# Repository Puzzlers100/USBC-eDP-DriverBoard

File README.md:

## __USBC-eDP Driver Board__  

This project works to adapt a USB-C DisplayPort alt-mode input into an embedded DisplayPort output. It uses an STM32 to communicate over the USB-C Power delivery protocol, acts as a USB Hub providing one USB 3.0 Superspeed port and 2 USB 2.0 High Speed ports. It also negotiates the highest current available from the source, and internally generates the 12V needed to run the display.  It works by simply routing the same DP signals through to the output, and does no signal processing of it's own. 
## USE  

It should work with most 30pin eDP panels. Since it has no native processing on it's own, the DP generation is set by the computer and panel used. Generally, this allows for up to 1080p panels. Exceptionally large or exceptionally bright panels may not work, as those panels tend to draw a large current on the 12V rail. I highly recommend sticking to panels that draw a continuous current of no more than 800mA for the backlight.

The STM32 provides PWM dimming capability by using the potentiometer on the daughter board. If you want to remove this capability, short pin 1 to pin 2 on J2 (This is a temporary solution, the plan is to in the future specify which brightness control scheme should be used using R25 and R26)

Personally, I am using the Innolux N116BCA-EA1 panel with a 3D printed case published in the Mechanical folder. If you would prefer a 1080p panel, the AUO G116HAN looks like it should also fit the case, however I do not have one to test with. 

#### NOTICE
The USB 2.0 ports are configured to run outside of the USB specification. They claim to be able to provide up to 500mA of current, however trigger overcurrent protection at 250mA. This can be fixed by replacing line 17 in i2C_comms.c with {0x18, 0x20, 0x01}, however the incorrect version can be useful with higher power flash drives that require 200mA, which was the reason I chose to do it this way.
## BUILD INFO

#### PCBs
BOMs for both the main board and secondary board are in the electrical folder, and contain all the parts required to build a fully functional PCB.  The main board is specifically designed to be manufactured using JLC-PCBs JLC04081H-3313 stackup, as the USB lines are impedance matched, and the generated gerber files are designed to be used with JLC. The potentiometer board has no such restrictions, but I recommend using a 0.8mm PCB. Currently there is no pick and place support, so you will need to hand solder the PCBs. The passives should be rated for at least 12V

## Firmware
The firmware is written using the STMCube Ide. To get the PCB to work, you need to compile it using cube IDE, then upload it to the STM32 using either a J-link or STlink. If you have a TagConnect TC2030, there is a pad connector available on the PCB, if not, the pads are big enough you could solder on some leads to them.

## FFC cables
The design uses a Type A, 4pin, 0.5mm pitch FFC cable to connect the main board and pot board. For my design, I used a 10cm long cable, though what length you need may depend on your chosen LCD and layout

You will also require a 30 pin eDP cable. I used a 250mm one for my design.

## Hardware
The mechanical design is published as a set of solidworks files as well as a set of 3MFs. The 3MFs were made for the Prusa MK3S+ with the MMU2, though they will likely work with most slicers and printers that support multi filament printing. They are designed to be printed in PETG with appropriate scaling to account for shrinkage. A couple of the parts also have support blocks with a PLA interface so they should be removable. 

To fully assemble the enclosure, you will need:

- 19x [M2 4.8mm Wide, 1.5mm thick nuts](https://www.mcmaster.com/92513A110/)
- 13x [M2 10mm Countersunk Screw](https://www.mcmaster.com/90236A106/)
- 17x [M2 6mm Countersunk Screw](https://www.mcmaster.com/90236A104/)
- 13x [M2 4mm Countersunk Screw](https://www.mcmaster.com/90236A102/) 
	
## TODO
Future Plans are mostly in the software:
 - USB HID interface for brightness control and notifications
 - Proper current monitoring and active over-current protection control by reducing screen brightness
 - Use R25 and R26 resistors to define which brightness control method is desired.
 - Redesign the enclosure to use metal nuts. I just used some nuts I had on hand that I thought were M2 but are actually probably M2.5

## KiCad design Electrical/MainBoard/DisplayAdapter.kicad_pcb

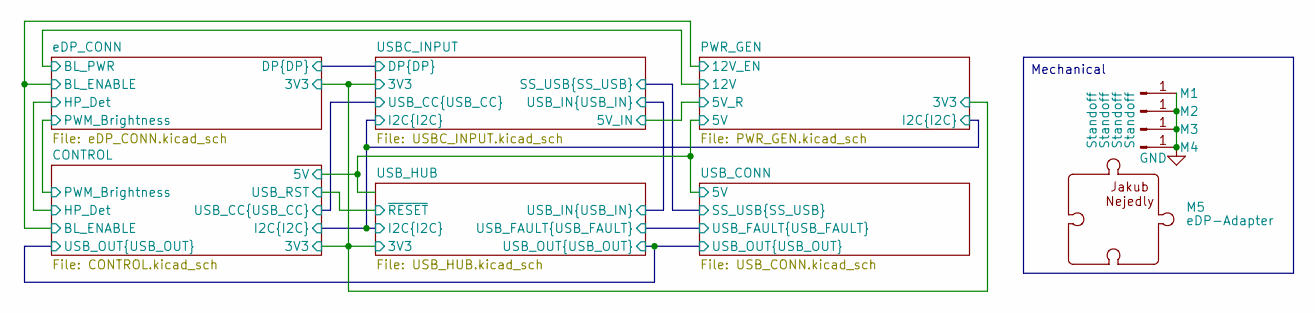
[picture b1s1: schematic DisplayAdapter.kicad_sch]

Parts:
M1, M2, M3, M4: Standoff; MS04-M2-2
M5: eDP-Adapter; Logo

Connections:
GND: M1.1, M2.1, M3.1, M4.1; also elsewhere on the board

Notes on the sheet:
Mechanical

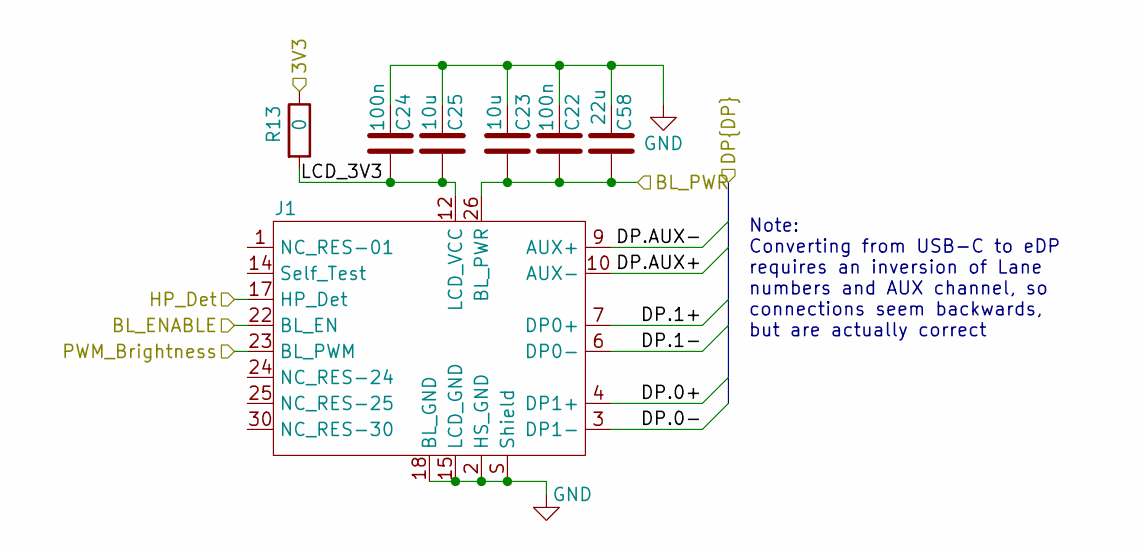
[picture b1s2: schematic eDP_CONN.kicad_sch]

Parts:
C22, C24: 100n; 0603_C
C23, C25: 10u; 0603_C
C58: 22u; 0603_C
J1: 30_Pin_Zif; FH19SC-30S-0.5SH(09)
R13: 0; 0805_R

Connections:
/CONTROL/3V3: R13.1; also elsewhere on the board
/CONTROL/BL_ENABLE: J1.22 (BL_EN); also elsewhere on the board
/CONTROL/HP_Det: J1.17 (HP_Det); also elsewhere on the board
/CONTROL/PWM_Brightness: J1.23 (BL_PWM); also elsewhere on the board
/PWR_GEN/12V: C22.2, C23.2, C58.2, J1.26 (BL_PWR), J1.27 (BL_PWR), J1.28 (BL_PWR), J1.29 (BL_PWR); also elsewhere on the board
/USBC_INPUT/DP.0+: J1.4 (DP1+); also elsewhere on the board
/USBC_INPUT/DP.0-: J1.3 (DP1-); also elsewhere on the board
/USBC_INPUT/DP.1+: J1.7 (DP0+); also elsewhere on the board
/USBC_INPUT/DP.1-: J1.6 (DP0-); also elsewhere on the board
/USBC_INPUT/DP.AUX+: J1.10 (AUX-); also elsewhere on the board
/USBC_INPUT/DP.AUX-: J1.9 (AUX+); also elsewhere on the board
/eDP_CONN/LCD_3V3: C24.1, C25.1, J1.12 (LCD_VCC), J1.13 (LCD_VCC), R13.2
GND: C22.1, C23.1, C24.2, C25.2, C58.1, J1.2 (HS_GND), J1.5 (HS_GND), J1.8 (HS_GND), J1.11 (HS_GND), J1.15 (LCD_GND), J1.16 (LCD_GND), J1.18 (BL_GND), J1.19 (BL_GND), J1.20 (BL_GND), J1.21 (BL_GND), J1.S (Shield); also elsewhere on the board

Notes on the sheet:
Note: Converting from USB-C to eDP requires an inversion of Lane numbers and AUX channel, so connections seem backwards, but are actually correct

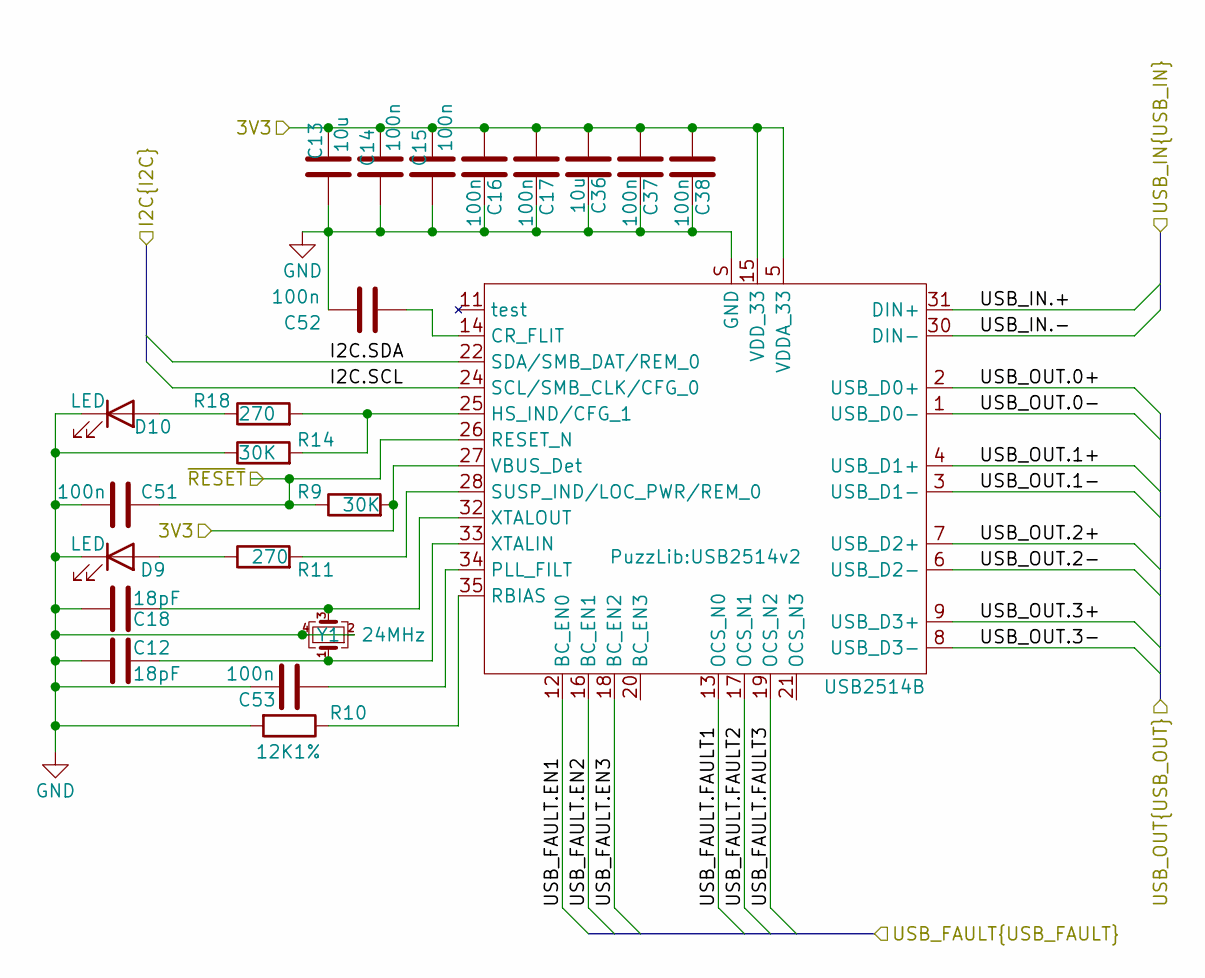
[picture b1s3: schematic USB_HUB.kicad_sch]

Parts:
C12, C18: 18pF; 0603_C
C13, C36: 10u; 0603_C
C14, C15, C16, C17, C37, C38, C51, C52, C53: 100n; 0603_C
D9, D10: LED; LTST_Diode
R9, R14: 30K; 0603_R
R10: 12K1%; 0603_R
R11, R18: 270; 0603_R
U5: USB2514B; USB2514v2
Y1: 24MHz; FA-128_OSC

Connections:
/CONTROL/3V3: C13.2, C14.2, C15.2, C16.2, C17.2, C36.2, C37.2, C38.2, R9.2, U5.5 (VDDA_33), U5.10 (VDDA_33), U5.15 (VDD_33), U5.23 (VDD_33), U5.27 (VBUS_Det), U5.29 (VDDA_33), U5.36 (VDDA_33); also elsewhere on the board
/CONTROL/I2C.SCL: U5.24 (SCL/SMB_CLK/CFG_0); also elsewhere on the board
/CONTROL/I2C.SDA: U5.22 (SDA/SMB_DAT/REM_0); also elsewhere on the board
/CONTROL/USB_OUT.0+: U5.2 (USB_D0+); also elsewhere on the board
/CONTROL/USB_OUT.0-: U5.1 (USB_D0-); also elsewhere on the board
/CONTROL/USB_OUT.1+: U5.4 (USB_D1+); also elsewhere on the board
/CONTROL/USB_OUT.1-: U5.3 (USB_D1-); also elsewhere on the board
/CONTROL/USB_OUT.2+: U5.7 (USB_D2+); also elsewhere on the board
/CONTROL/USB_OUT.2-: U5.6 (USB_D2-); also elsewhere on the board
/CONTROL/USB_OUT.3+: U5.9 (USB_D3+); also elsewhere on the board
/CONTROL/USB_OUT.3-: U5.8 (USB_D3-); also elsewhere on the board
/CONTROL/USB_RST: C51.1, R9.1, U5.26 (RESET_N); also elsewhere on the board
/USBC_INPUT/USB_IN.+: U5.31 (DIN+); also elsewhere on the board
/USBC_INPUT/USB_IN.-: U5.30 (DIN-); also elsewhere on the board
/USB_CONN/USB_FAULT.EN1: U5.12 (BC_EN0); also elsewhere on the board
/USB_CONN/USB_FAULT.EN2: U5.16 (BC_EN1); also elsewhere on the board
/USB_CONN/USB_FAULT.EN3: U5.18 (BC_EN2); also elsewhere on the board
/USB_CONN/USB_FAULT.FAULT1: U5.13 (OCS_N0); also elsewhere on the board
/USB_CONN/USB_FAULT.FAULT2: U5.17 (OCS_N1); also elsewhere on the board
/USB_CONN/USB_FAULT.FAULT3: U5.19 (OCS_N2); also elsewhere on the board
GND: C12.2, C13.1, C14.1, C15.1, C16.1, C17.1, C18.2, C36.1, C37.1, C38.1, C51.2, C52.2, C53.2, D9.1 (K), D10.1 (K), R10.2, R14.1, U5.S (GND), Y1.2, Y1.4; also elsewhere on the board
unnamed: D9.2 (A), R11.1
unnamed: D10.2 (A), R18.1
unnamed: C52.1, U5.14 (CR_FLIT)
unnamed: R14.2, R18.2, U5.25 (HS_IND/CFG_1)
unnamed: C53.1, U5.34 (PLL_FILT)
unnamed: R10.1, U5.35 (RBIAS)
unnamed: R11.2, U5.28 (SUSP_IND/LOC_PWR/REM_0)
unnamed: C12.1, U5.33 (XTALIN), Y1.1
unnamed: C18.1, U5.32 (XTALOUT), Y1.3

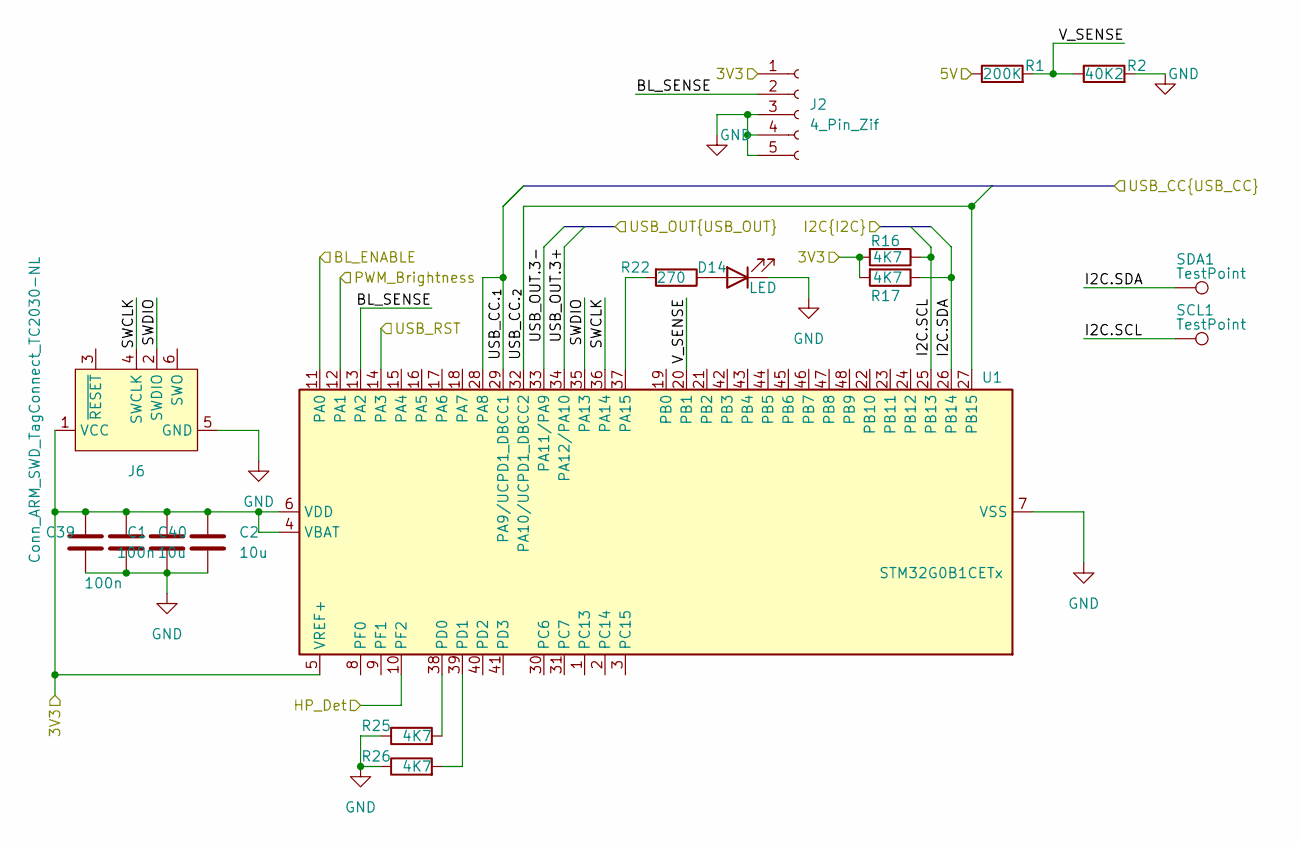
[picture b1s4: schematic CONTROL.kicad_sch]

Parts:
C1, C39: 100n; 0603_C
C2, C40: 10u; 0603_C
D14: LED; LTST_Diode
J2: 4_Pin_Zif; FH19C-4S-0.5SH(10)
J6: Conn_ARM_SWD_TagConnect_TC2030-NL; Tag-Connect_TC2030-IDC-NL_2x03_P1.27mm_Vertical
R1: 200K; 0603_R
R2: 40K2; 0603_R
R16, R17, R25, R26: 4K7; 0603_R
R22: 270; 0603_R
SCL1: TestPoint; TestPoint_Pad_D1.0mm
SDA1: TestPoint; TestPoint_Pad_D1.0mm
U1: STM32G0B1CETx; LQFP-48_7x7mm_P0.5mm

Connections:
/CONTROL/3V3: C1.1, C2.1, C39.1, C40.1, J2.1, J6.1 (VCC), R16.2, R17.2, U1.4 (VBAT), U1.5 (VREF+), U1.6 (VDD); also elsewhere on the board
/CONTROL/BL_ENABLE: U1.11 (PA0); also elsewhere on the board
/CONTROL/BL_SENSE: J2.2, U1.13 (PA2)
/CONTROL/HP_Det: U1.10 (PF2); also elsewhere on the board
/CONTROL/I2C.SCL: R16.1, SCL1.1, U1.25 (PB13); also elsewhere on the board
/CONTROL/I2C.SDA: R17.1, SDA1.1, U1.26 (PB14); also elsewhere on the board
/CONTROL/PWM_Brightness: U1.12 (PA1); also elsewhere on the board
/CONTROL/SWCLK: J6.4 (SWCLK), U1.36 (PA14)
/CONTROL/SWDIO: J6.2 (SWDIO), U1.35 (PA13)
/CONTROL/USB_CC._{1}: U1.28 (PA8), U1.29 (PA9/UCPD1_DBCC1); also elsewhere on the board
/CONTROL/USB_CC._{2}: U1.27 (PB15), U1.32 (PA10/UCPD1_DBCC2); also elsewhere on the board
/CONTROL/USB_OUT.3+: U1.34 (PA12/PA10); also elsewhere on the board
/CONTROL/USB_OUT.3-: U1.33 (PA11/PA9); also elsewhere on the board
/CONTROL/USB_RST: U1.14 (PA3); also elsewhere on the board
/CONTROL/V_SENSE: R1.2, R2.1, U1.20 (PB1)
/PWR_GEN/5V: R1.1; also elsewhere on the board
GND: C1.2, C2.2, C39.2, C40.2, D14.1 (K), J2.3, J2.4, J2.5, J6.5 (GND), R2.2, R25.1, R26.1, U1.7 (VSS); also elsewhere on the board
unnamed: D14.2 (A), R22.1
unnamed: R22.2, U1.37 (PA15)
unnamed: R25.2, U1.38 (PD0)
unnamed: R26.2, U1.39 (PD1)

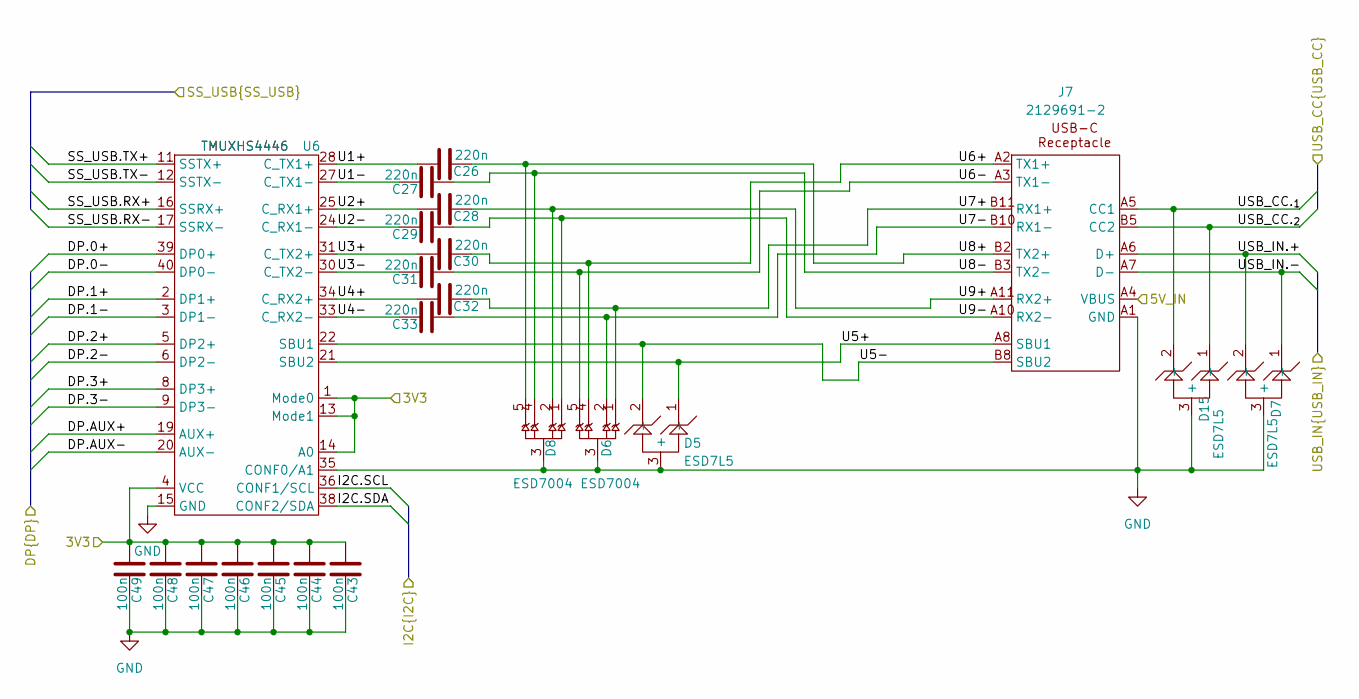
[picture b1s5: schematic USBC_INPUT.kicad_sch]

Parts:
C26, C27, C28, C29, C30, C31, C32, C33: 220n; 0402_C
C43, C44, C45, C46, C47, C48, C49: 100n; 0402_C
D5, D7, D15: ESD7L5
D6, D8: ESD7004
J7: 2129691-2; 2129691-2_2.8mmOut
U6: TMUXHS4446

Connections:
/CONTROL/3V3: C43.2, C44.2, C45.2, C46.2, C47.2, C48.2, C49.2, U6.1 (Mode0), U6.4 (VCC), U6.7, U6.10, U6.13 (Mode1), U6.14 (A0), U6.23, U6.26, U6.29, U6.32; also elsewhere on the board
/CONTROL/I2C.SCL: U6.36 (CONF1/SCL); also elsewhere on the board
/CONTROL/I2C.SDA: U6.38 (CONF2/SDA); also elsewhere on the board
/CONTROL/USB_CC._{1}: D15.2 (-), J7.A5 (CC1); also elsewhere on the board
/CONTROL/USB_CC._{2}: D15.1 (-), J7.B5 (CC2); also elsewhere on the board
/PWR_GEN/5V_R: J7.A4 (VBUS), J7.A9, J7.B4, J7.B9; also elsewhere on the board
/USBC_INPUT/DP.0+: U6.39 (DP0+); also elsewhere on the board
/USBC_INPUT/DP.0-: U6.40 (DP0-); also elsewhere on the board
/USBC_INPUT/DP.1+: U6.2 (DP1+); also elsewhere on the board
/USBC_INPUT/DP.1-: U6.3 (DP1-); also elsewhere on the board
/USBC_INPUT/DP.2+: U6.5 (DP2+)
/USBC_INPUT/DP.2-: U6.6 (DP2-)
/USBC_INPUT/DP.3+: U6.8 (DP3+)
/USBC_INPUT/DP.3-: U6.9 (DP3-)
/USBC_INPUT/DP.AUX+: U6.19 (AUX+); also elsewhere on the board
/USBC_INPUT/DP.AUX-: U6.20 (AUX-); also elsewhere on the board
/USBC_INPUT/SS_USB.RX+: U6.16 (SSRX+); also elsewhere on the board
/USBC_INPUT/SS_USB.RX-: U6.17 (SSRX-); also elsewhere on the board
/USBC_INPUT/SS_USB.TX+: U6.11 (SSTX+); also elsewhere on the board
/USBC_INPUT/SS_USB.TX-: U6.12 (SSTX-); also elsewhere on the board
/USBC_INPUT/U1+: C26.2, U6.28 (C_TX1+)
/USBC_INPUT/U1-: C27.2, U6.27 (C_TX1-)
/USBC_INPUT/U2+: C28.2, U6.25 (C_RX1+)
/USBC_INPUT/U2-: C29.2, U6.24 (C_RX1-)
/USBC_INPUT/U3+: C30.2, U6.31 (C_TX2+)
/USBC_INPUT/U3-: C31.2, U6.30 (C_TX2-)
/USBC_INPUT/U4+: C32.2, U6.34 (C_RX2+)
/USBC_INPUT/U4-: C33.2, U6.33 (C_RX2-)
/USBC_INPUT/U5+: D5.1 (-), J7.A8 (SBU1), U6.21 (SBU2)
/USBC_INPUT/U5-: D5.2 (-), J7.B8 (SBU2), U6.22 (SBU1)
/USBC_INPUT/U6+: C30.1, D6.4, D6.7, J7.A2 (TX1+)
/USBC_INPUT/U6-: C31.1, D6.5, D6.6, J7.A3 (TX1-)
/USBC_INPUT/U7+: C32.1, D6.1, D6.10, J7.B11 (RX1+)
/USBC_INPUT/U7-: C33.1, D6.2, D6.9, J7.B10 (RX1-)
/USBC_INPUT/U8+: C26.1, D8.5, D8.6, J7.B2 (TX2+)
/USBC_INPUT/U8-: C27.1, D8.4, D8.7, J7.B3 (TX2-)
/USBC_INPUT/U9+: C28.1, D8.2, D8.9, J7.A11 (RX2+)
/USBC_INPUT/U9-: C29.1, D8.1, D8.10, J7.A10 (RX2-)
/USBC_INPUT/USB_IN.+: D7.2 (-), J7.A6 (D+), J7.B6; also elsewhere on the board
/USBC_INPUT/USB_IN.-: D7.1 (-), J7.A7 (D-), J7.B7; also elsewhere on the board
GND: C43.1, C44.1, C45.1, C46.1, C47.1, C48.1, C49.1, D5.3 (+), D6.3, D6.8, D7.3 (+), D8.3, D8.8, D15.3 (+), J7.A1 (GND), J7.A12, J7.B1, J7.B12, J7.S, U6.15 (GND), U6.18, U6.35 (CONF0/A1), U6.37, U6.41; also elsewhere on the board

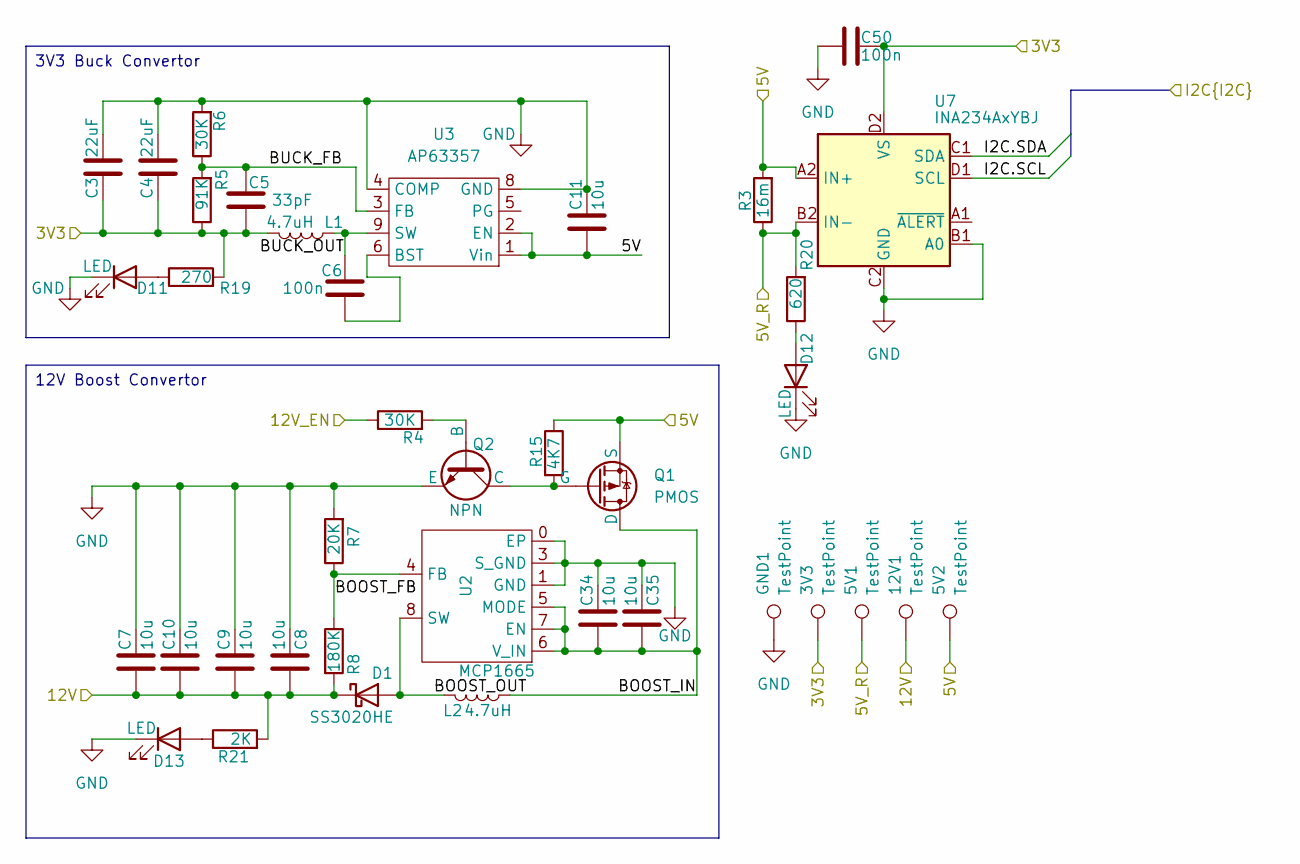
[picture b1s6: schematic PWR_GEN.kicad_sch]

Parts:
3V3, 5V1, 5V2, 12V1: TestPoint; TestPoint_Pad_D1.0mm
C3, C4: 22uF; 0603_C
C5: 33pF; 0603_C
C6: 100n; 0603_C
C7, C8, C9, C10, C11, C34, C35: 10u; 0603_C
C50: 100n; 0402_C
D1: SS3020HE
D11, D12, D13: LED; LTST_Diode
GND1: TestPoint; TestPoint_Pad_D1.0mm
L1, L2: 4.7uH; XGL4018_Inductor
Q1: PMOS; TSOT-23
Q2: NPN; TSOT-23
R3: 16m; 0612_R_v2
R4, R6: 30K; 0603_R
R5: 91K; 0603_R
R7: 20K; 0603_R
R8: 180K; 0603_R
R15: 4K7; 0603_R
R19: 270; 0603_R
R20: 620; 0603_R
R21: 2K; 0603_R
U2: MCP1665
U3: AP63357
U7: INA234AxYBJ; INA234

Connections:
/CONTROL/3V3: 3V3.1, C3.1, C4.1, C5.2, C50.1, L1.2, R5.1, R19.2, U7.D2 (VS); also elsewhere on the board
/CONTROL/BL_ENABLE: R4.1; also elsewhere on the board
/CONTROL/I2C.SCL: U7.D1 (SCL); also elsewhere on the board
/CONTROL/I2C.SDA: U7.C1 (SDA); also elsewhere on the board
/PWR_GEN/5V: 5V2.1, C11.2, Q1.2 (S), R3.2, R15.1, U3.1 (Vin), U3.2 (EN), U7.A2 (IN+); also elsewhere on the board
/PWR_GEN/5V_R: 5V1.1, R3.1, R20.2, U7.B2 (IN-); also elsewhere on the board
/PWR_GEN/12V: 12V1.1, C7.2, C8.2, C9.2, C10.2, D1.1 (K), R8.2, R21.2; also elsewhere on the board
/PWR_GEN/BOOST_FB: R7.1, R8.1, U2.4 (FB)
/PWR_GEN/BOOST_IN: C34.2, C35.2, L2.1, Q1.3 (D), U2.5 (MODE), U2.6 (V_IN), U2.7 (EN)
/PWR_GEN/BOOST_OUT: D1.2 (A), L2.2, U2.8 (SW), U2.9
/PWR_GEN/BUCK_FB: C5.1, R5.2, R6.1, U3.3 (FB)
/PWR_GEN/BUCK_OUT: C6.2, L1.1, U3.7 (NC), U3.9 (SW)
GND: C3.2, C4.2, C7.1, C8.1, C9.1, C10.1, C11.1, C34.1, C35.1, C50.2, D11.1 (K), D12.1 (K), D13.1 (K), GND1.1, Q2.2 (E), R6.2, R7.2, U2.0 (EP), U2.1 (GND), U2.2, U2.3 (S_GND), U2.10, U3.4 (COMP), U3.8 (GND), U7.B1 (A0), U7.C2 (GND); also elsewhere on the board
unnamed: D11.2 (A), R19.1
unnamed: D12.2 (A), R20.1
unnamed: D13.2 (A), R21.1
unnamed: Q1.1 (G), Q2.3 (C), R15.2
unnamed: Q2.1 (B), R4.2
unnamed: C6.1, U3.6 (BST)

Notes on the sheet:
12V Boost Convertor
3V3 Buck Convertor

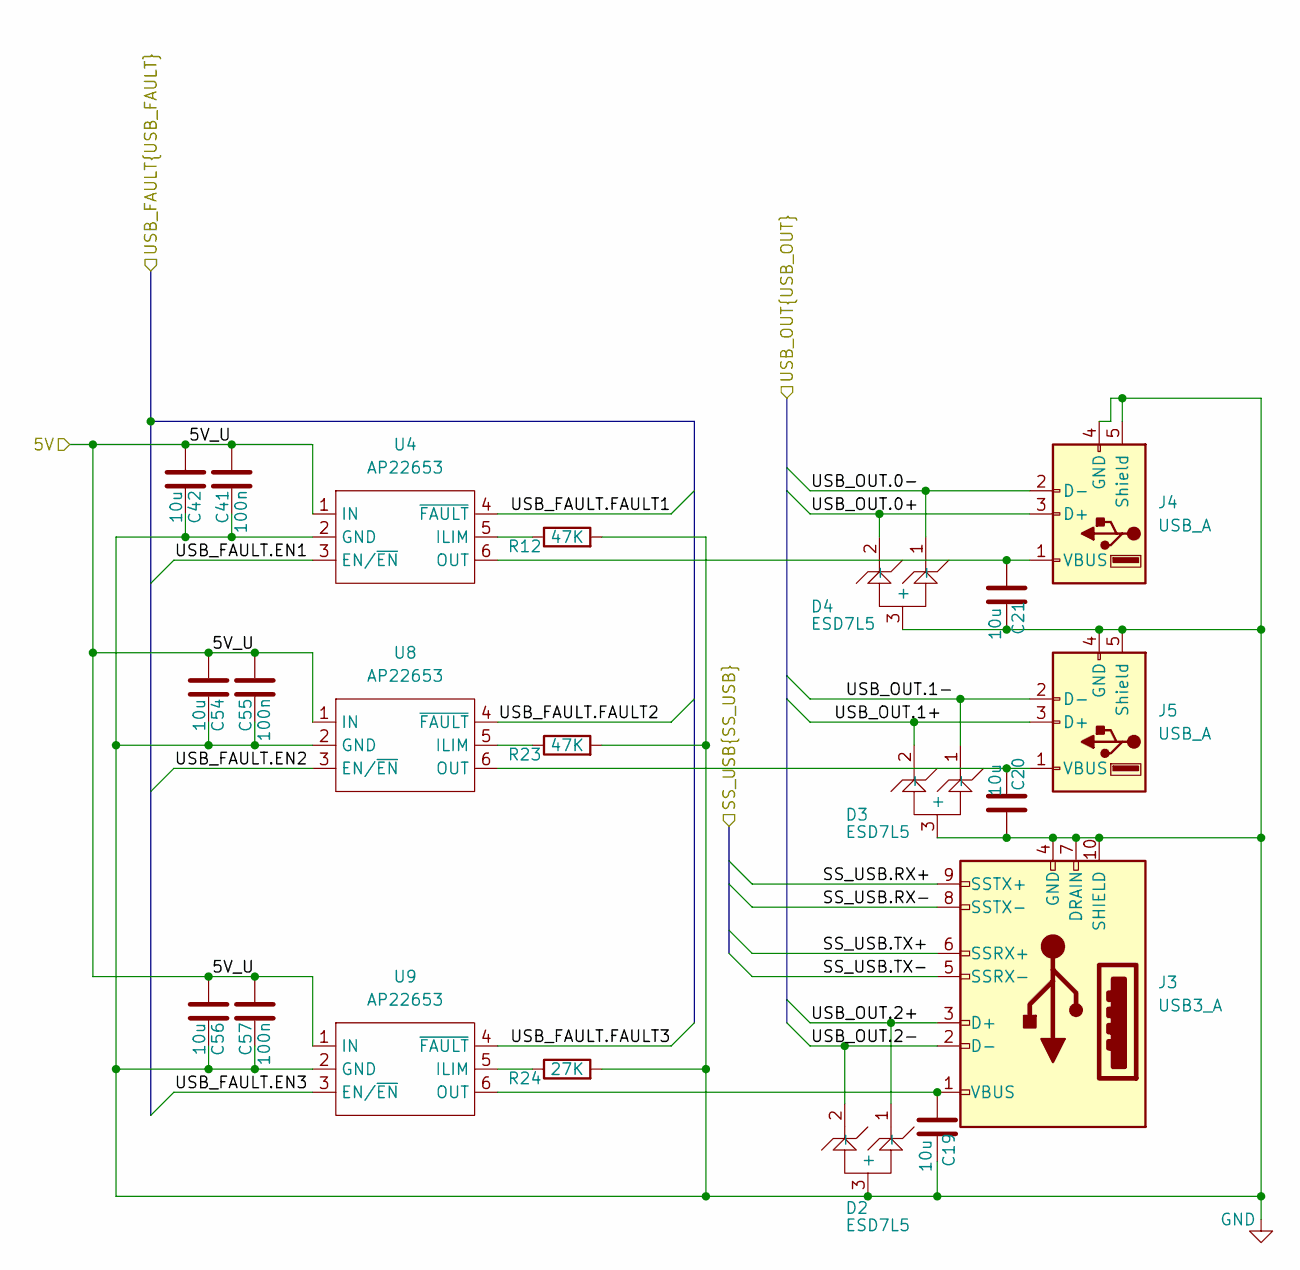
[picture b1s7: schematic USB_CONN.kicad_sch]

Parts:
C19, C20, C21, C42, C54, C56: 10u; 0603_C
C41, C55, C57: 100n; 0603_C
D2, D3, D4: ESD7L5
J3: USB3_A; USBA32_692121230100v2_1.6mmOut
J4, J5: USB_A; USB1015v2_1.6mmOut
R12, R23: 47K; 0603_R
R24: 27K; 0603_R
U4, U8, U9: AP22653; AP22652-DFN

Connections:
/CONTROL/USB_OUT.0+: D4.2 (-), J4.3 (D+); also elsewhere on the board
/CONTROL/USB_OUT.0-: D4.1 (-), J4.2 (D-); also elsewhere on the board
/CONTROL/USB_OUT.1+: D3.2 (-), J5.3 (D+); also elsewhere on the board
/CONTROL/USB_OUT.1-: D3.1 (-), J5.2 (D-); also elsewhere on the board
/CONTROL/USB_OUT.2+: D2.1 (-), J3.3 (D+); also elsewhere on the board
/CONTROL/USB_OUT.2-: D2.2 (-), J3.2 (D-); also elsewhere on the board
/PWR_GEN/5V: C41.1, C42.1, C54.1, C55.1, C56.1, C57.1, U4.1 (IN), U8.1 (IN), U9.1 (IN); also elsewhere on the board
/USBC_INPUT/SS_USB.RX+: J3.9 (SSTX+); also elsewhere on the board
/USBC_INPUT/SS_USB.RX-: J3.8 (SSTX-); also elsewhere on the board
/USBC_INPUT/SS_USB.TX+: J3.6 (SSRX+); also elsewhere on the board
/USBC_INPUT/SS_USB.TX-: J3.5 (SSRX-); also elsewhere on the board
/USB_CONN/USB_FAULT.EN1: U4.3 (EN/~EN); also elsewhere on the board
/USB_CONN/USB_FAULT.EN2: U8.3 (EN/~EN); also elsewhere on the board
/USB_CONN/USB_FAULT.EN3: U9.3 (EN/~EN); also elsewhere on the board
/USB_CONN/USB_FAULT.FAULT1: U4.4 (~FAULT); also elsewhere on the board
/USB_CONN/USB_FAULT.FAULT2: U8.4 (~FAULT); also elsewhere on the board
/USB_CONN/USB_FAULT.FAULT3: U9.4 (~FAULT); also elsewhere on the board
GND: C19.2, C20.2, C21.2, C41.2, C42.2, C54.2, C55.2, C56.2, C57.2, D2.3 (+), D3.3 (+), D4.3 (+), J3.4 (GND), J3.7 (DRAIN), J3.10 (SHIELD), J4.4 (GND), J4.5 (Shield), J5.4 (GND), J5.5 (Shield), R12.2, R23.2, R24.2, U4.2 (GND), U4.S, U8.2 (GND), U8.S, U9.2 (GND), U9.S; also elsewhere on the board
unnamed: C19.1, J3.1 (VBUS), U9.6 (OUT)
unnamed: C21.1, J4.1 (VBUS), U4.6 (OUT)
unnamed: C20.1, J5.1 (VBUS), U8.6 (OUT)
unnamed: R12.1, U4.5 (ILIM)
unnamed: R23.1, U8.5 (ILIM)
unnamed: R24.1, U9.5 (ILIM)

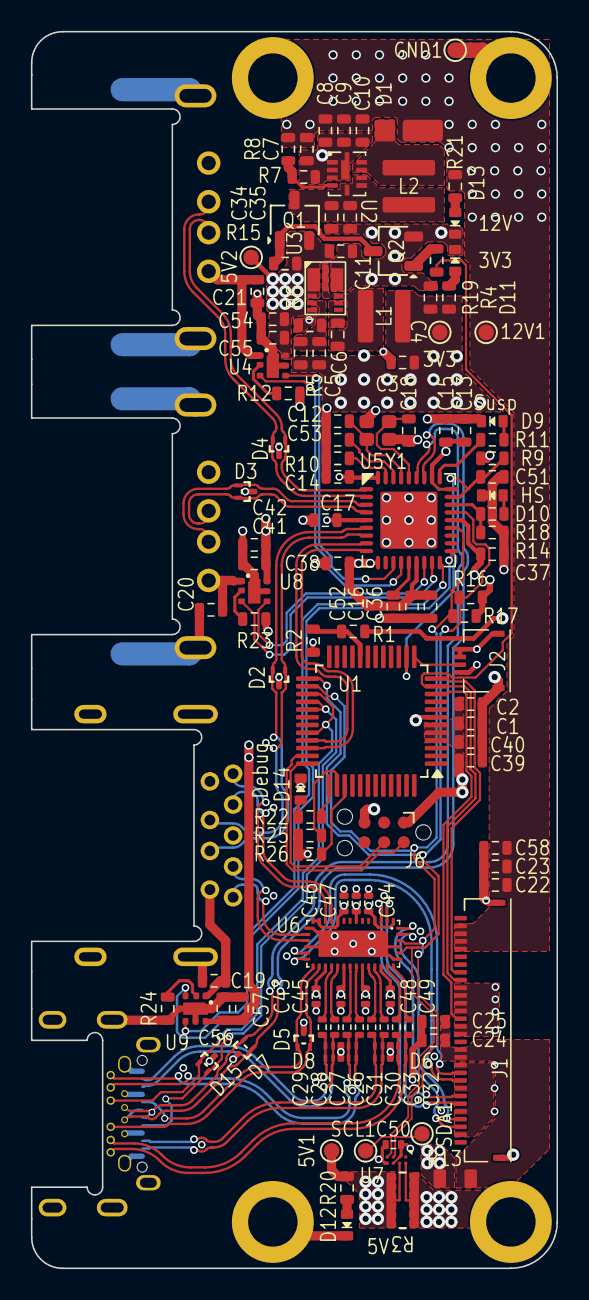
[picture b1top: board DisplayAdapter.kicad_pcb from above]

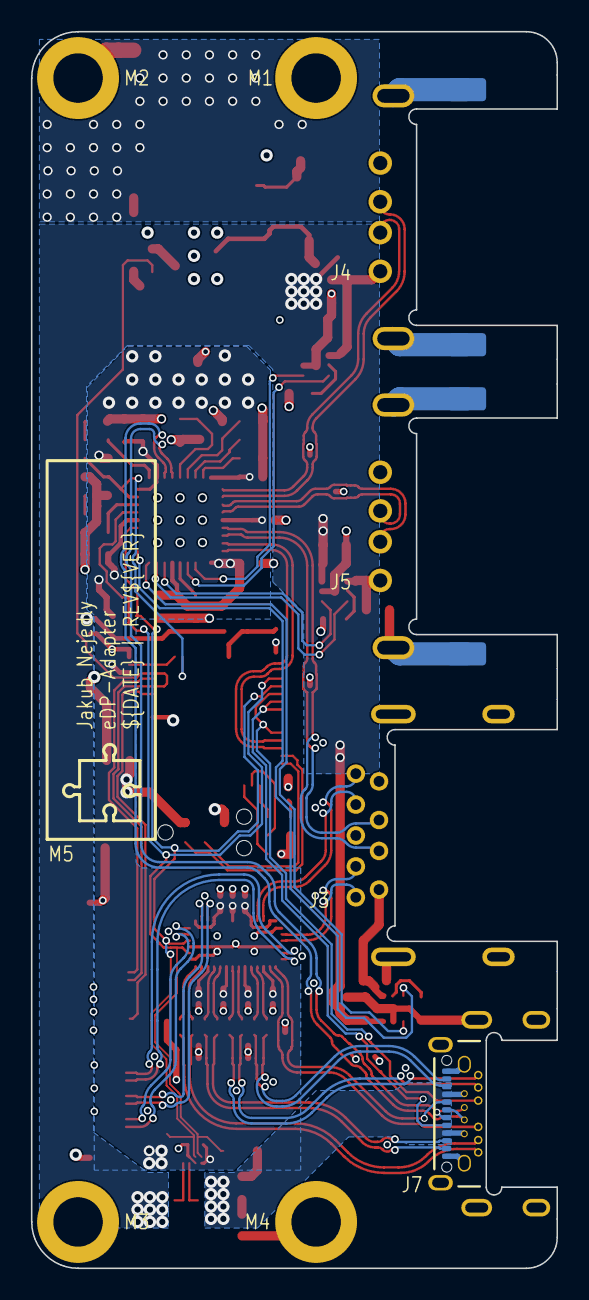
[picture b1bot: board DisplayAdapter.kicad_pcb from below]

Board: 4 copper layers, 34.0 x 80.0 mm, 132 parts (9 on the bottom side), 92 nets.

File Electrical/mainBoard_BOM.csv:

Id;Designator;Footprint;Quantity;Designation;Manufacturer;Ref
1;C1,C39,C38,C16,C51,C55,C14,C41,C17,C52,C24,C53,C57,C6,C22,C37,C15;0603_C;17;100n;;
2;C25,C11,C54,C23,C35,C42,C2,C56,C8,C13,C19,C21,C9,C36,C7,C40,C34,C10,C20;0603_C;19;10u;;
3;J2;FH19C-4S-0.5SH(10);1;4_Pin_Zif;Hirose;FH19C-4S-0.5SH(10)
4;Q2;TSOT-23;1;NPN;onsemi;NSS40201LT1G
5;R9,R6,R4,R14;0603_R;4;30K;;
6;D13,D12,D9,D11,D10,D14;LTST_Diode;6;LED;LITE-ON;S270GTK
7;C44,C47,C43,C50,C46,C45,C49,C48;0402_C;8;100n;;
8;C58;0603_C;1;22u;;
9;R5;0603_R;1;91K;;
10;R1;0603_R;1;200K;;
11;L2,L1;XGL4018_Inductor;2;4.7uH;Coilcraft;XGL4018
12;R13;0805_R;1;0;;
13;Q1;TSOT-23;1;PMOS;Vishay;SQ2303CES-T1_BE3
14;R17,R16,R25,R26,R15;0603_R;5;4K7;;
15;U4,U8,U9;AP22652-DFN;3;AP22653;Diodes Inc;AP22653FDZ-7
16;R7;0603_R;1;20K;;
17;U6;TMUXHS4446;1;TMUXHS4446;Texas Instruments;TMUXHS4446RETR
18;R2;0603_R;1;40K2;;
19;U7;INA234;1;INA234AxYBJ;Texas Instruments;INA234AIYBJR
20;D7,D3,D15,D2,D5,D4;ESD7L5;6;ESD7L5;onsemi;ESD7L5.0DT5G
21;R12,R23;0603_R;2;47K;;
22;C32,C31,C28,C26,C27,C30,C29,C33;0402_C;8;220n;;
23;C4,C3;0603_C;2;22uF;;
24;R11,R22,R18,R19;0603_R;4;270;;
25;D8,D6;ESD7004;2;ESD7004;onsemi;ESD7004MUTAG
26;J1;FH19SC-30S-0.5SH(09);1;30_Pin_Zif;hirose;FH19SC-30S-0.5SH(09)
27;U1;LQFP-48_7x7mm_P0.5mm;1;STM32G0B1CETx;ST Micro;STM32G0B1CET6
28;R10;0603_R;1;12K1%;;
29;R21;0603_R;1;2K;;
30;D1;SS3020HE;1;SS3020HE;Panjit international;SS3020HE_R1_00001
31;Y1;FA-128_OSC;1;24MHz;EPSON;FA-128 24.0000MF10Z-W0
32;C12,C18;0603_C;2;18pF;;
33;R8;0603_R;1;180K;;
34;C5;0603_C;1;33pF;;
35;U2;MCP1665;1;MCP1665;Microchip;MCP1665T-E/MRA
36;U5;USB2514v2;1;USB2514B;Microchip;USB2514B/M2
37;U3;AP63357;1;AP63357;Diodes Inc;AP63357DV-7
38;R20;0603_R;1;620;;
39;R3;0612_R_v2;1;16m;YAGEO;PE0612FKF070R016L
40;R24;0603_R;1;27K;;
41;J3;USBA32_692121230100v2_1.6mmOut;1;USB3_A;Wurth Elektronik;692121230100
42;J7;2129691-2_2.8mmOut;1;2129691-2;TE Connectivity;2129691-2
43;J5,J4;USB1015v2_1.6mmOut;2;USB_A;GCT;USB1015-GF-L-A
44;M4,M2,M3,M1;MS04-M2-2;4;Standoff;PEM;MSO4-M2-2

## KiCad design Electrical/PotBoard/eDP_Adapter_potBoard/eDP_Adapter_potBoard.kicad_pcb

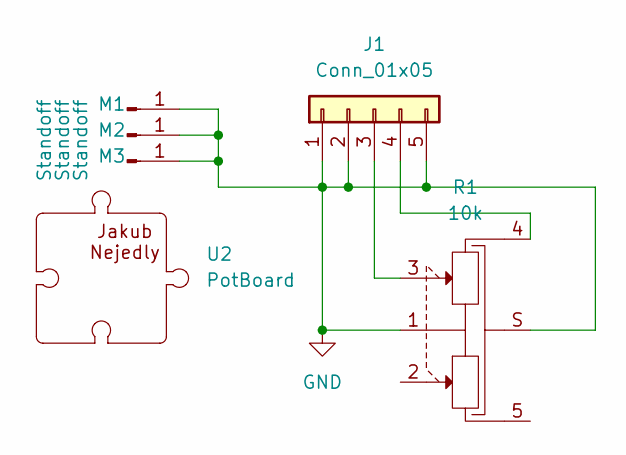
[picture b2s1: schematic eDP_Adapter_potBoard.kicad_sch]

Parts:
J1: Conn_01x05; FH19C-4S-0.5SH(10)
M1, M2, M3: Standoff; MS04-M2-2
R1: 10k; RK10J12R0A0B
U2: PotBoard; Logo_SMALL

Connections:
GND: J1.1, J1.2, J1.5, M1.1, M2.1, M3.1, R1.1, R1.S
unnamed: J1.3, R1.3
unnamed: J1.4, R1.4

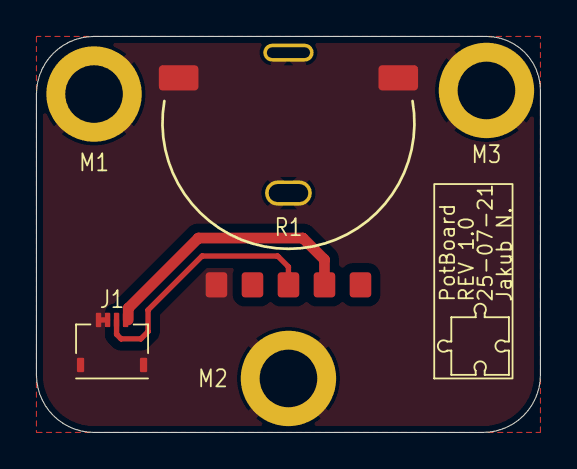
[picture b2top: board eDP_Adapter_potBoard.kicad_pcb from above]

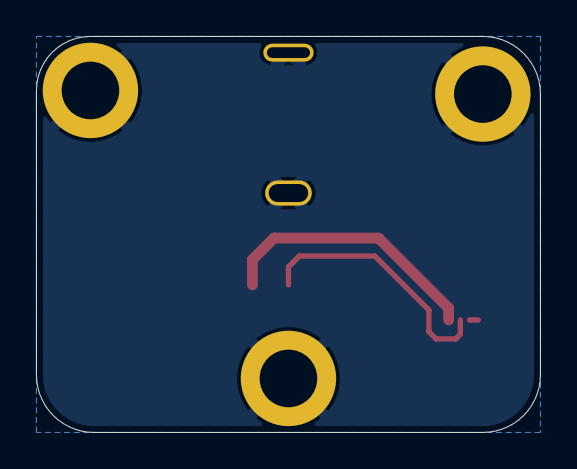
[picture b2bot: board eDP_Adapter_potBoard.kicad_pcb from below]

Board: 2 copper layers, 28.0 x 22.0 mm, 6 parts (3 on the bottom side), 3 nets.

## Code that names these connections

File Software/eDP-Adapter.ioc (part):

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Mcu.Name=STM32G0B1C(B-C-E)Tx
Mcu.Package=LQFP48
Mcu.UserName=STM32G0B1CETx
PA0.GPIOParameters=GPIO_Label
PA0.GPIO_Label=BL_Enable
PA0.Signal=GPIO_Output
PA1.GPIOParameters=GPIO_Label
PA1.GPIO_Label=BL_PWM
PA1.Signal=S_TIM2_CH2
PA10.Mode=EnableDeadBattery
PA10.Signal=UCPD1_DBCC2
PA13.Mode=Serial_Wire
PA13.Signal=SYS_SWDIO
PA14-BOOT0.Mode=Serial_Wire
PA14-BOOT0.Signal=SYS_SWCLK
PA15.GPIOParameters=GPIO_Label
PA15.GPIO_Label=DEBUG
PA15.Signal=GPIO_Output
PA2.GPIOParameters=GPIO_Label
PA2.GPIO_Label=BL_Sense
PA2.Mode=IN2
PA2.Signal=ADC1_IN2
PA8.Mode=Sink_AllSignals
PA8.Signal=UCPD1_CC1
PA9.Mode=EnableDeadBattery
PA9.Signal=UCPD1_DBCC1
PB1.GPIOParameters=GPIO_Label
PB1.GPIO_Label=V_Sense
PB1.Mode=IN9
PB1.Signal=ADC1_IN9
PB13.Mode=I2C
PB13.Signal=I2C2_SCL
PB14.Mode=I2C
PB14.Signal=I2C2_SDA
PB15.Mode=Sink_AllSignals
PB15.Signal=UCPD1_CC2
PD0.GPIOParameters=GPIO_PuPd,GPIO_Label
PD0.GPIO_Label=VER0
PD0.GPIO_PuPd=GPIO_PULLUP
PD0.Signal=GPIO_Input
PD1.GPIOParameters=GPIO_PuPd,GPIO_Label
PD1.GPIO_Label=VER1
PD1.GPIO_PuPd=GPIO_PULLUP
PD1.Signal=GPIO_Input
RCC.HSE_VALUE=8000000
RCC.SYSCLKFreq_VALUE=48000000
RCC.SYSCLKSource=RCC_SYSCLKSOURCE_PLLCLK
board=custom

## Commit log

2025-10-29 Initialized the Repo and Began the Readme
2025-11-25 Added Functional Branch of the Software
2025-11-25 UNTESTED: WORKING ON CURRENT TRACKING
2025-11-25 Imported Electrical Hardware
2026-01-07 Fixed Font issues
2026-01-07 Partial Readme
2026-01-07 BOM and fixed potboard font
2026-01-07 Fixed Gitignore typo
2026-01-07 Added Mechanical components, fixed electrical err
2026-01-07 didn't know how tabs worked
2026-01-07 fixed readme formatting
2026-01-07 ReadMe
2026-01-07 typo in monitor
